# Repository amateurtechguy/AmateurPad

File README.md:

# AmateurPad
A 3x3 macropad that lets you get extra shortcuts without having to do any extra work, and also helps you adjust the volume at night without looking for the volume up volume down button with it's rotary encoder!

## What is This?
It is a custom macropad powered by a Seeed XIAO RP2040 microcontroller and QMK Firmware, allowing it to be fully customizable and compact.

Have you ever felt like you need more keys, want a little hack station, or simply just irritated from having to click so many buttons just to open github or your calculator or notes?

Well AmateurPad is for you! Cause with AmateurPad you can write your thoughts down with one click, way before you forget about them quickly!

## Features:

- 3x3 Matrix for 9 beautiful sounding keys
- One Rotary Encoder that you can twist and press to your hearts desire
- Custom PCB to eliminate the need for messy wires
- A 3D printed Case for accessibility and ease
- Custom QMK Firmware which allows easy reprogramming

### The PCB 

### The schematic

### The 3D Model

#### Made With Kicad!

## Preset Functions:

(My custom firmware comes with these settings included, but feel free to change it to better meet your needs!)

### Rotary Encoder:

| Turn Left	| Turn Right |	Press |
|-----------|------------|--------|
| Volume Up |	Volume Down	| Toggle Layers |
| Brightness Up | Brightness Down | Toggle Layers |

### Keys Base Layer:

|    |Col 1| Col 2	| Col 3 |
|----|-----|--------|-------|
|Row 1| Calculator |	GitHub | Notes |
|Row 2|	Esc | Delete | Alt |
|Row 3|	Ctrl |	space |	Enter |

### Keys Numpad Layer:

|    |Col 1| Col 2	| Col 3 |
|----|-----|--------|-------|
|Row 1| 1 |	4 | 7 |
|Row 2|	2 | 5 | 8 |
|Row 3|	3 |	6 |	9 |

## How To Use:

Download QMK on laptop or pc.

then click [here](https://docs.qmk.fm/newbs_flashing) for detailed instructions on how to flash it!

## What I Learned:
- How to design start to finish my own project
- How to design my own schematics and import footprints based on real world parts
- How to properly arrange my components on a PCB and wire them accordingly
- How to design 3D objects from scratch
- How to interpret Docs effectively in order to turn my knowledge into code
- How to ask for help when I need it from my Hack Club Community

---
## Creator:
made by the amateur tech guy:D

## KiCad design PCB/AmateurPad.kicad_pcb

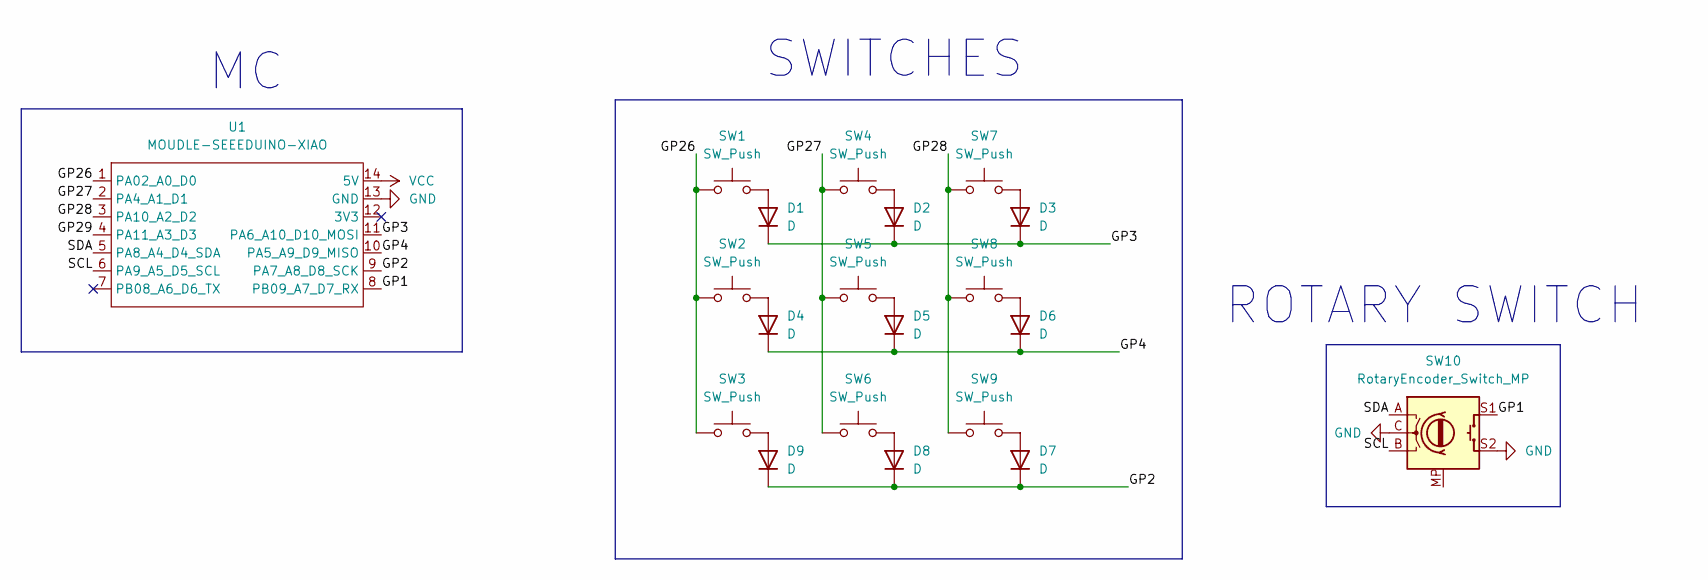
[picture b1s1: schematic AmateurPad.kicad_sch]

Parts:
D1, D2, D3, D4, D5, D6, D7, D8, D9: D; D_DO-35_SOD27_P7.62mm_Horizontal
SW1, SW2, SW3, SW4, SW5, SW6, SW7, SW8, SW9: SW_Push; SW_Cherry_MX_1.00u_PCB
SW10: RotaryEncoder_Switch_MP; RotaryEncoder_Alps_EC11E-Switch_Vertical_H20mm
U1: MOUDLE-SEEEDUINO-XIAO; XIAO-Generic-Hybrid-14P-2.54-21X17.8MM

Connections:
/GP1: SW10.S1, U1.8 (PB09_A7_D7_RX)
/GP2: D7.1 (K), D8.1 (K), D9.1 (K), U1.9 (PA7_A8_D8_SCK)
/GP3: D1.1 (K), D2.1 (K), D3.1 (K), U1.11 (PA6_A10_D10_MOSI)
/GP4: D4.1 (K), D5.1 (K), D6.1 (K), U1.10 (PA5_A9_D9_MISO)
/GP26: SW1.1, SW2.1, SW3.1, U1.1 (PA02_A0_D0)
/GP27: SW4.1, SW5.1, SW6.1, U1.2 (PA4_A1_D1)
/GP28: SW7.1, SW8.1, SW9.1, U1.3 (PA10_A2_D2)
/GP29: U1.4 (PA11_A3_D3)
/SCL: SW10.B, U1.6 (PA9_A5_D5_SCL)
/SDA: SW10.A, U1.5 (PA8_A4_D4_SDA)
GND: SW10.C, SW10.S2, U1.13 (GND)
unnamed: D1.2 (A), SW1.2
unnamed: D2.2 (A), SW4.2
unnamed: D3.2 (A), SW7.2
unnamed: D4.2 (A), SW2.2
unnamed: D5.2 (A), SW5.2
unnamed: D6.2 (A), SW8.2
unnamed: D7.2 (A), SW9.2
unnamed: D8.2 (A), SW6.2
unnamed: D9.2 (A), SW3.2
VCC: U1.14 (5V)

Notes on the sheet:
ROTARY SWITCH
SWITCHES

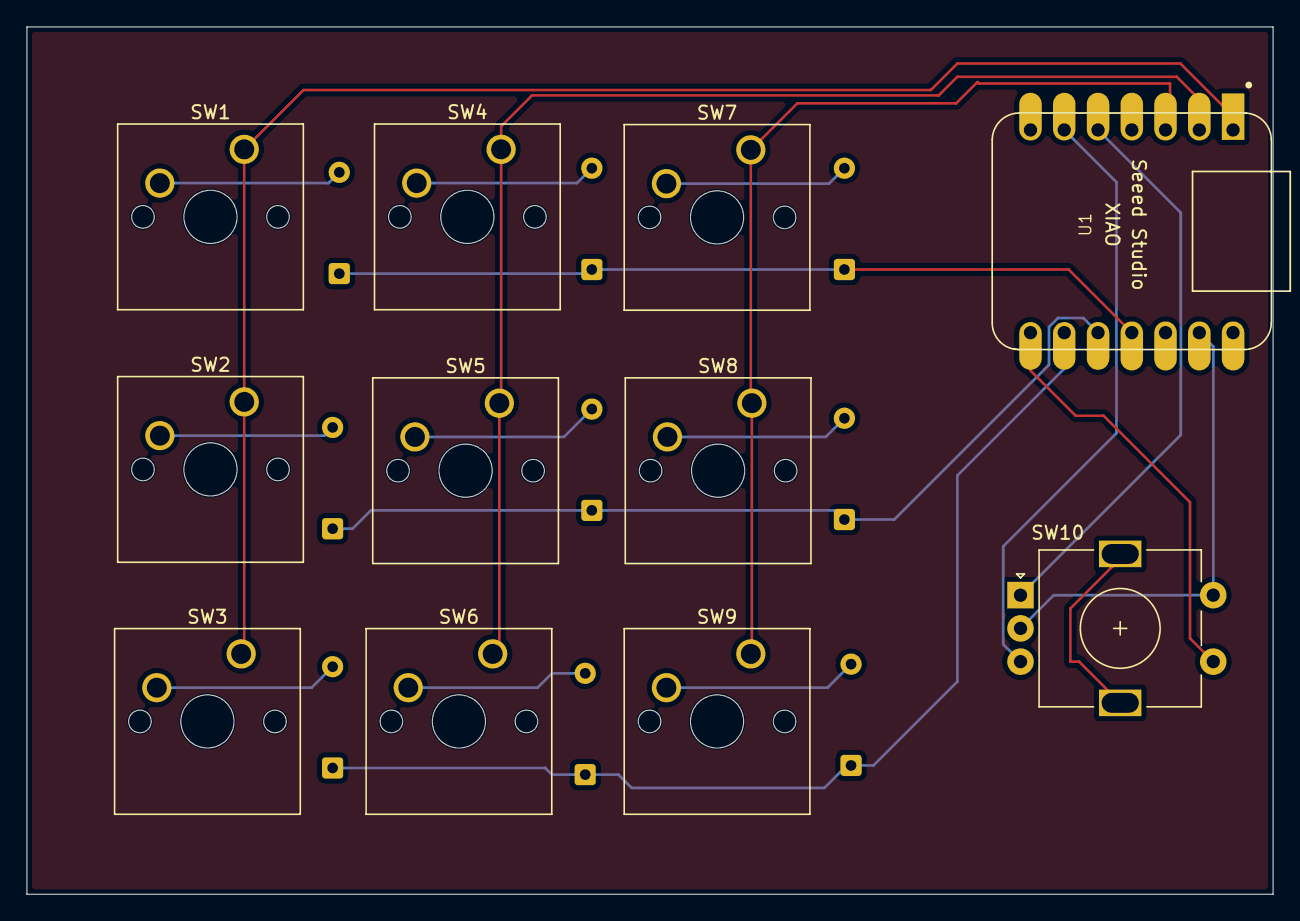
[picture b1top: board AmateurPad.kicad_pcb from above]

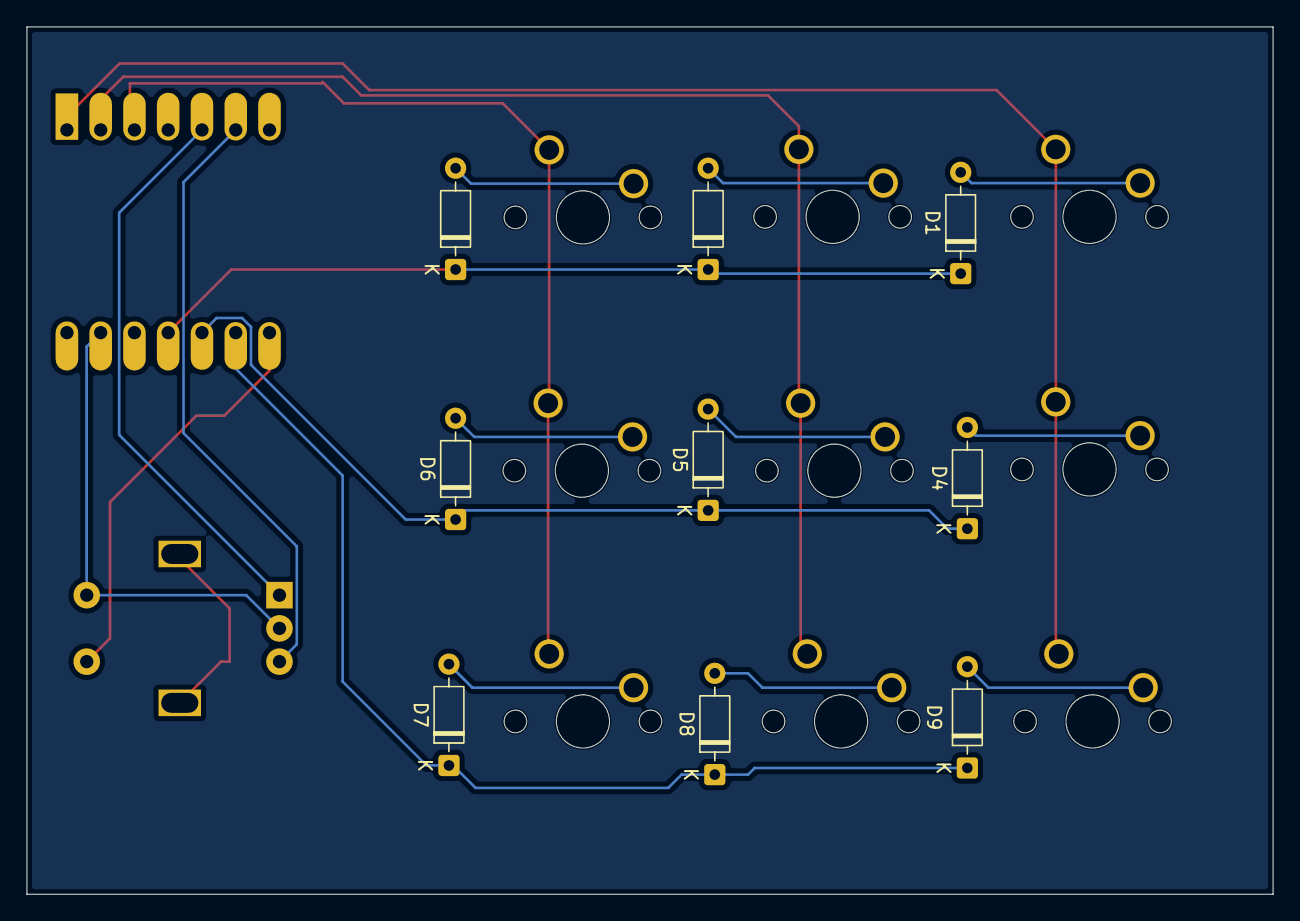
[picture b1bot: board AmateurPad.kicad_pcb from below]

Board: 2 copper layers, 93.8 x 65.2 mm, 20 parts (9 on the bottom side), 19 nets.
